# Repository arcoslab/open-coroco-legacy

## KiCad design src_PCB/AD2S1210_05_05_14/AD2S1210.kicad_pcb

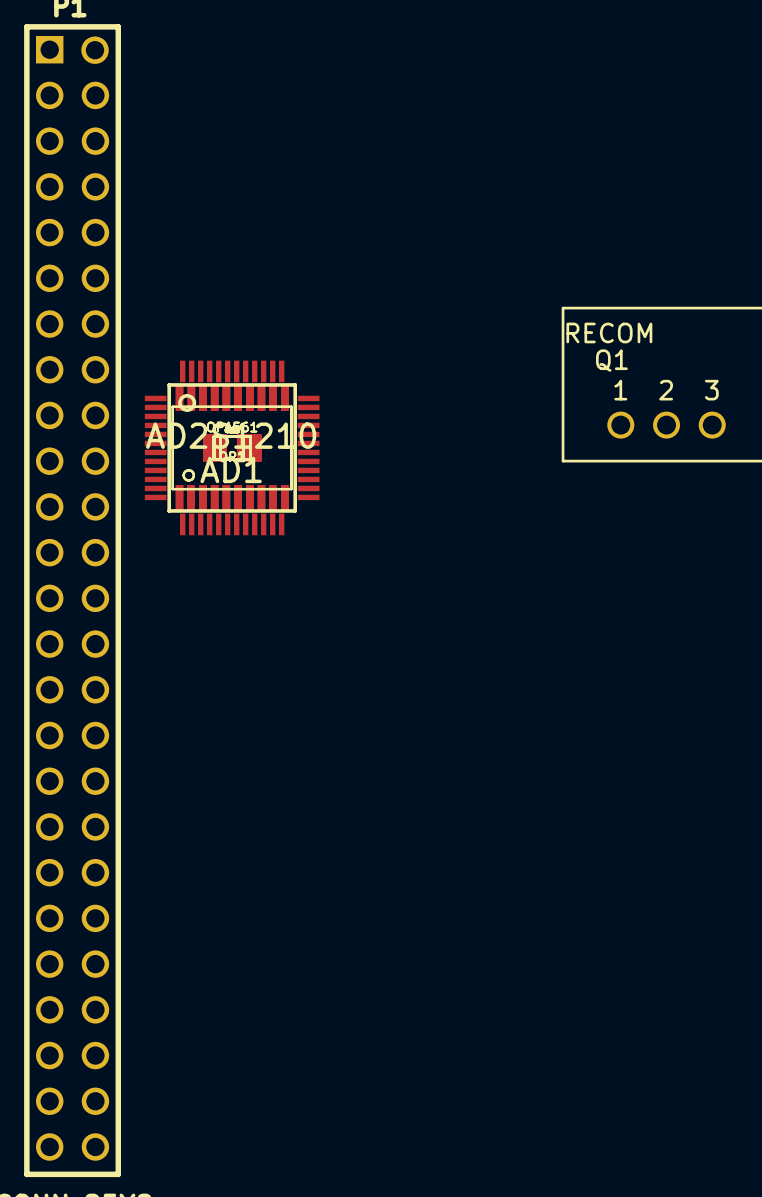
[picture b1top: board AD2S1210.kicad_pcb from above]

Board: 2 copper layers, 29 parts (0 on the bottom side), 40 nets, no tracks yet.

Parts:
AD1: AD2S1210; LQFP48
C2, C3, C5, C9, C18: 10n; c_0805
C4, C8: 20p; c_0805
C10: 4.7µ; c_0805
C11: 2.2µ; c_0805
C12, C13: 120p; c_0805
C16, C17: 100n; c_0805
OP1, OP2: OPA561; tssop-20
P1: CONN_25X2; PIN_ARRAY_STM32_25X2
Q1: RECOM; SIP-3
R1: 1k; c_0805
R2, R3: 15.4k; c_0805
R4, R5, R9, R11: 10k; c_0805
R6, R7: 390k; c_0805
R8, R10: 22k; c_0805

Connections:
/A0: AD1.36, AD1.37, P1.4, R1.1
/COS: AD1.45, P1.10
/COSLO: AD1.44, P1.12
/EXC: AD1.38, R5.1
/OUT_EXC: C13.1, OP2.7, P1.24, R3.1
/OUT_~EXC: C12.1, OP1.7, P1.22, R2.1
/SCLK: AD1.13, P1.38
/SDI: AD1.12, P1.40
/SDO: AD1.11, P1.37
/SIN: AD1.41, P1.18
/SINLO: AD1.42, P1.16
/V_DRIVE: AD1.3, P1.3
/~EXC: AD1.39, R4.1
/~SAMPLE: AD1.10, P1.9
/~WR: AD1.4, P1.13
GND: AD1.19, C16.2, C17.2, C18.2, OP1.5, OP2.5
unnamed: AD1.6, C3.2
unnamed: AD1.5, C3.1
unnamed: C9.2, C10.2
unnamed: AD1.18, C9.1, C10.1
unnamed: AD1.9, C4.2, C8.2
unnamed: C17.1, C18.1, Q1.2
unnamed: AD1.1, AD1.2, AD1.48, C2.2
unnamed: AD1.8, C8.1
unnamed: AD1.7, C4.1
unnamed: C16.1, Q1.1
unnamed: OP1.8, R6.2
unnamed: C12.2, OP1.3, R2.2, R4.2
unnamed: OP2.8, R7.2
unnamed: C13.2, OP2.3, R3.2, R5.2
unnamed: OP2.4, R11.2
unnamed: OP2.6, R7.1, R10.1
unnamed: AD1.33, C11.2, R1.2
unnamed: OP2.2, R10.2, R11.1
unnamed: AD1.43, C5.1
unnamed: AD1.40, C5.2
unnamed: AD1.46, C2.1
unnamed: OP1.2, R8.2, R9.1
unnamed: OP1.4, R9.2
unnamed: OP1.6, R6.1, R8.1

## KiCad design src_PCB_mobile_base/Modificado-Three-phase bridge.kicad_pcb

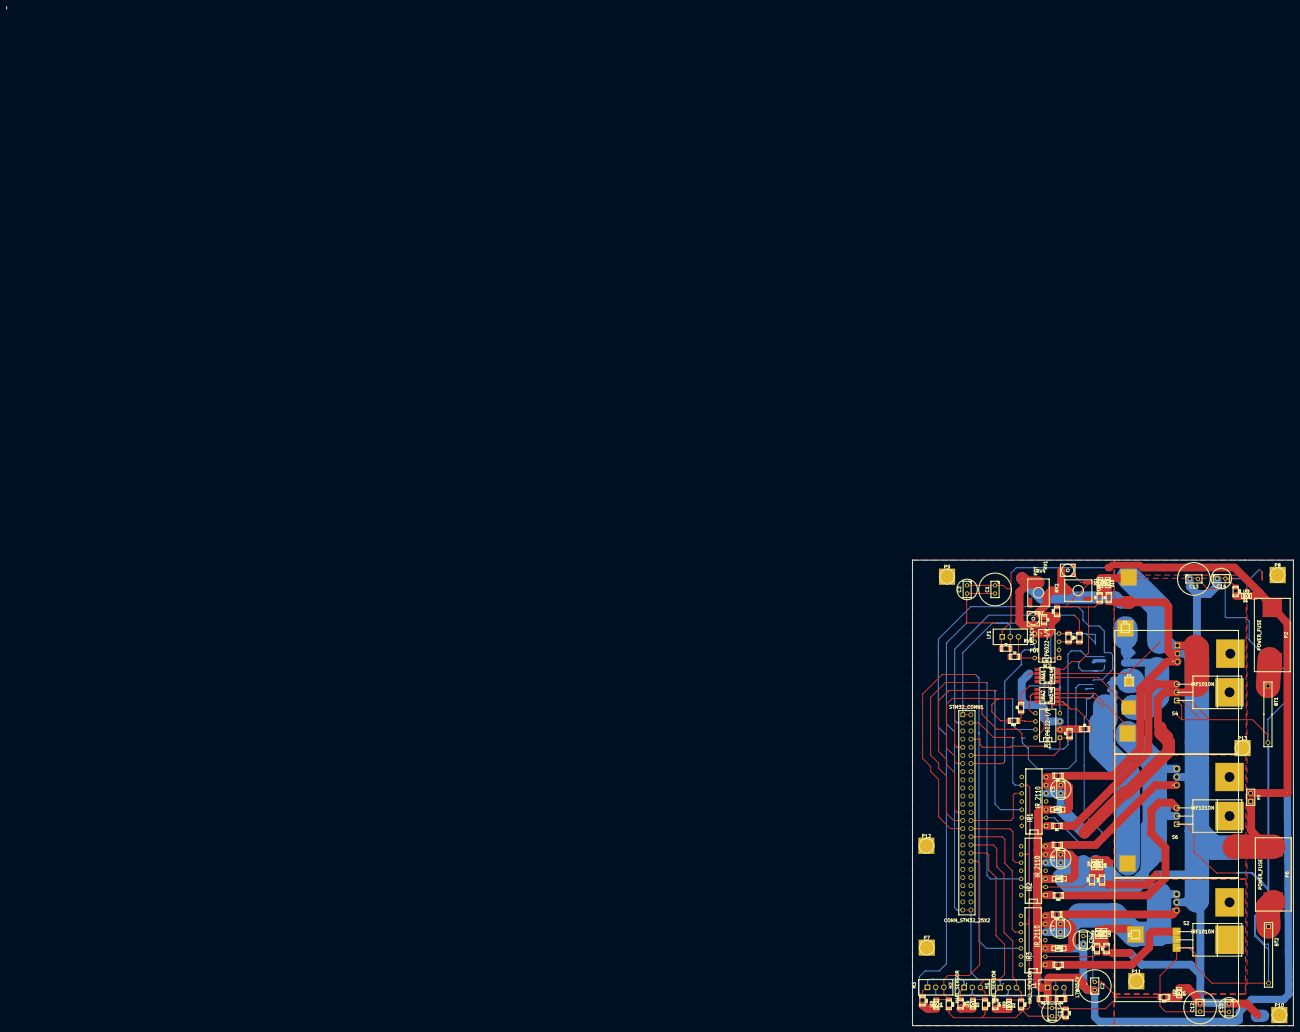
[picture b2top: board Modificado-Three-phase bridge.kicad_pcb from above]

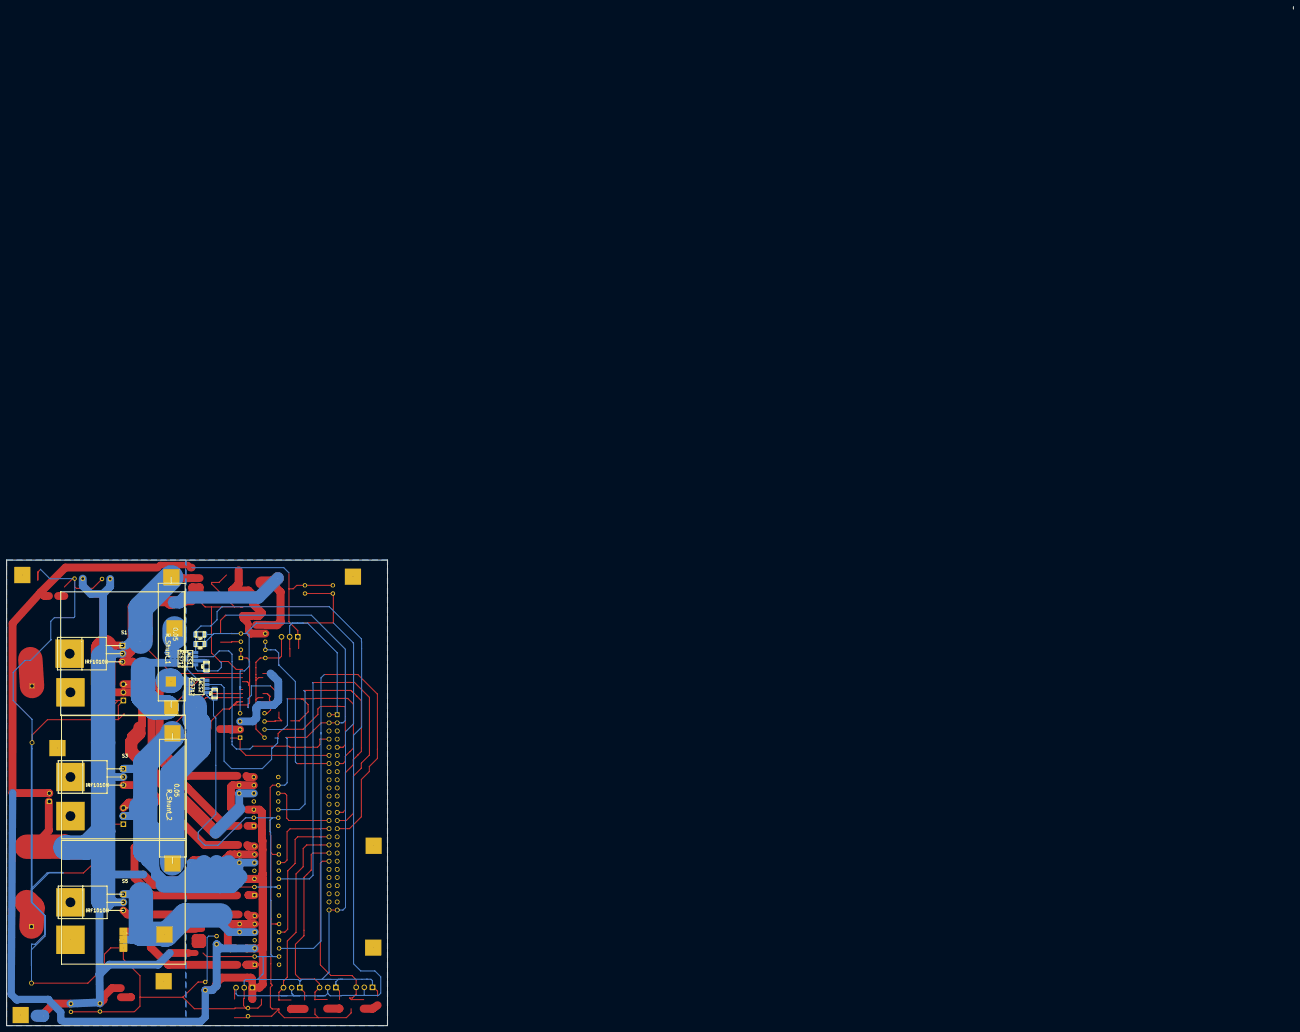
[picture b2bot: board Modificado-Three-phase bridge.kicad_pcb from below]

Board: 2 copper layers, 118.9 x 145.3 mm, 105 parts (11 on the bottom side), 61 nets.

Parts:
1N1, 1N2, 1N3: 1N4003; SOD-123
ACS1, ACS2: ACS712
BT1: BATTERY_12V; Battery_2x1
BT2: BATTERY_48; Battery_2x1
C1, C2, C12, C13: 1000uF; 10mm_C
C3, C4, C5, C6, C14, C15, C17: 100uF; 6mm_C
C7: 100u; 6mm_C
C8, C10, C18, C20: 0.1uF; c_1206
C9: 2.2uF; c_1206
C11: 0.33uF; c_1206
C16: 10uF; c_1206
C19, C21: 1nF; c_1206
D1, D2, D3, D4, D5, D6, D7, D8, D9, D10, D11: LED; LED-1206
H1, H2, H3: HALL_SENSOR; TO220_small_Heatsink_stand_reduced_area
INA1, INA2: INA148; INA_148
IR1, IR2, IR3: IR_2110; DIP-14__300
L1: L7805CV; TO220_small_Heatsink_stand_reduced_area
LF1: LF33CV; TO220_small_Heatsink_stand_reduced_area
M1, M2: MCP6022-I/P; DIP-8__300
P1, P4, P5: CONN_1; PIN_ARRAY_1
P2, P6: POWER_FUSE; fuse_holder_SMD
P3: CONN_2; pin_2
P7, P8, P9, P10, P11, P12, P13: CONN_1; 1pin
R1, R3, R5, R7, R8, R9, R10, R11, R12, R13, R15, R17, R18, R21, R22, R23, R24, R25, R26: 1k; R_1206
R2, R4, R14, R16, R19, R20: 36; R_1206
R6: 3.9k; R_1206
R27, R28: R; R_1206
RV1, RV3: POT; Trimmer_20K_1.5mmW_4.5mmL_3.8mmH
RV2, RV4: POT; Trimmer_100K_5.21mmW_6.71mmL
R_Shunt_1, R_Shunt_2: 0.05; R_Shunt
S1, S2, S3, S4, S5, S6: IRF1010N; TO220_Big_Heat_Sink_Drain_Sink
STM32_CONN1: CONN_STM32_25X2; PIN_ARRAY_STM32_25X2

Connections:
+3.3V: C9.1, INA1.7, INA2.7, LF1.2, M1.8, M2.8
+5V: ACS1.8, ACS2.8, C10.2, C18.1, C20.1, H1.3, H2.3, H3.3, L1.2
+48V: C12.1, C13.1, C14.1, C15.1, D5.1, P3.1, P6.1, R1.2, R6.1, R13.2, R17.2, RV3.1, RV4.1, S1.3, S3.3, S5.3
GND: ACS1.5, ACS2.5, BT1.2, BT2.2, C1.2, C2.2, C3.2, C4.2, C8.1, C9.2, C10.1, C11.1, C12.2, C13.2, C14.2, C15.2, C16.2, C17.2, C18.2, C19.2, C20.2, C21.2, H1.1, H2.1, H3.1, INA1.4, INA2.4, IR1.2, IR1.13, IR2.2, IR2.13, IR3.2, IR3.13, L1.3, LF1.3, M1.4, M2.4, R3.2, R10.1, R12.2, R15.2, R18.2, R24.2, R25.2, R26.2, R27.1, R28.2, RV1.2, RV2.2, S2.1, S4.1, S6.1, STM32_CONN1.1, STM32_CONN1.2, STM32_CONN1.49, STM32_CONN1.50
unnamed: IR3.12, STM32_CONN1.29
unnamed: D2.1, H1.2, R21.2, STM32_CONN1.34
unnamed: D3.1, H2.2, R22.2, STM32_CONN1.36
unnamed: IR1.10, STM32_CONN1.28
unnamed: IR1.1, R4.1
unnamed: IR1.7, R2.1
unnamed: 1N1.2, C5.1, IR1.6
unnamed: M2.6, M2.7, STM32_CONN1.14
unnamed: IR2.10, STM32_CONN1.30
unnamed: IR3.10, STM32_CONN1.32
unnamed: IR1.12, STM32_CONN1.25
unnamed: IR2.12, STM32_CONN1.27
unnamed: BT2.1, P6.2
unnamed: BT1.1, P2.2
unnamed: ACS1.6, C19.1
unnamed: M1.1, R9.2, STM32_CONN1.12
unnamed: D6.2, D7.1, R17.1, R18.1
unnamed: D8.2, D9.1, R13.1, R15.1
unnamed: INA2.6, M1.5
unnamed: D10.2, D11.1, R1.1, R3.1
unnamed: M1.7, R11.1, STM32_CONN1.13
unnamed: M2.5, R6.2, R10.2, RV1.1, RV2.1, RV3.2, RV4.2
unnamed: M2.3, R7.2, R12.1
unnamed: IR2.1, R16.1
unnamed: IR2.7, R14.1
unnamed: 1N2.2, C6.1, IR2.6
unnamed: ACS1.3, ACS1.4, INA1.2, R_Shunt_1.2
unnamed: IR3.1, R20.1
unnamed: IR3.7, R19.1
unnamed: 1N3.2, C7.1, IR3.6
unnamed: M1.6, R8.2, R11.2
unnamed: INA1.6, M1.3
unnamed: M1.2, R5.2, R9.1
unnamed: D4.1, H3.2, R23.2, STM32_CONN1.38
unnamed: ACS1.7, STM32_CONN1.8
unnamed: C6.2, D8.1, D9.2, INA2.3, IR2.5, R_Shunt_2.1, S3.1, S6.3
unnamed: C5.2, D10.1, D11.2, INA1.3, IR1.5, R_Shunt_1.1, S1.1, S4.3
unnamed: C7.2, D6.1, D7.2, IR3.5, P5.1, S2.3, S5.1
unnamed: ACS1.1, ACS1.2, P1.1
unnamed: ACS2.1, ACS2.2, P4.1
unnamed: ACS2.3, ACS2.4, INA2.2, R_Shunt_2.2
unnamed: ACS2.6, C21.1
unnamed: D5.2, R27.2
unnamed: D1.2, R28.1
unnamed: ACS2.7, STM32_CONN1.9
unnamed: R14.2, S3.2
unnamed: INA1.1, INA2.1, M2.1, M2.2, R5.1, R8.1
unnamed: R16.2, S6.2
unnamed: R2.2, S1.2
unnamed: R4.2, S4.2
unnamed: R20.2, S2.2
unnamed: R19.2, S5.2
unnamed: D3.2, R25.1
unnamed: D4.2, R26.1
unnamed: D2.2, R24.1
VCC: 1N1.1, 1N2.1, 1N3.1, C1.1, C2.1, C3.1, C4.1, C8.2, C11.2, D1.1, IR1.3, IR2.3, IR3.3, L1.1, LF1.1, P2.1, P3.2
VDD: C16.1, C17.1, IR1.9, IR2.9, IR3.9, R7.1, R21.1, R22.1, R23.1, STM32_CONN1.3, STM32_CONN1.4

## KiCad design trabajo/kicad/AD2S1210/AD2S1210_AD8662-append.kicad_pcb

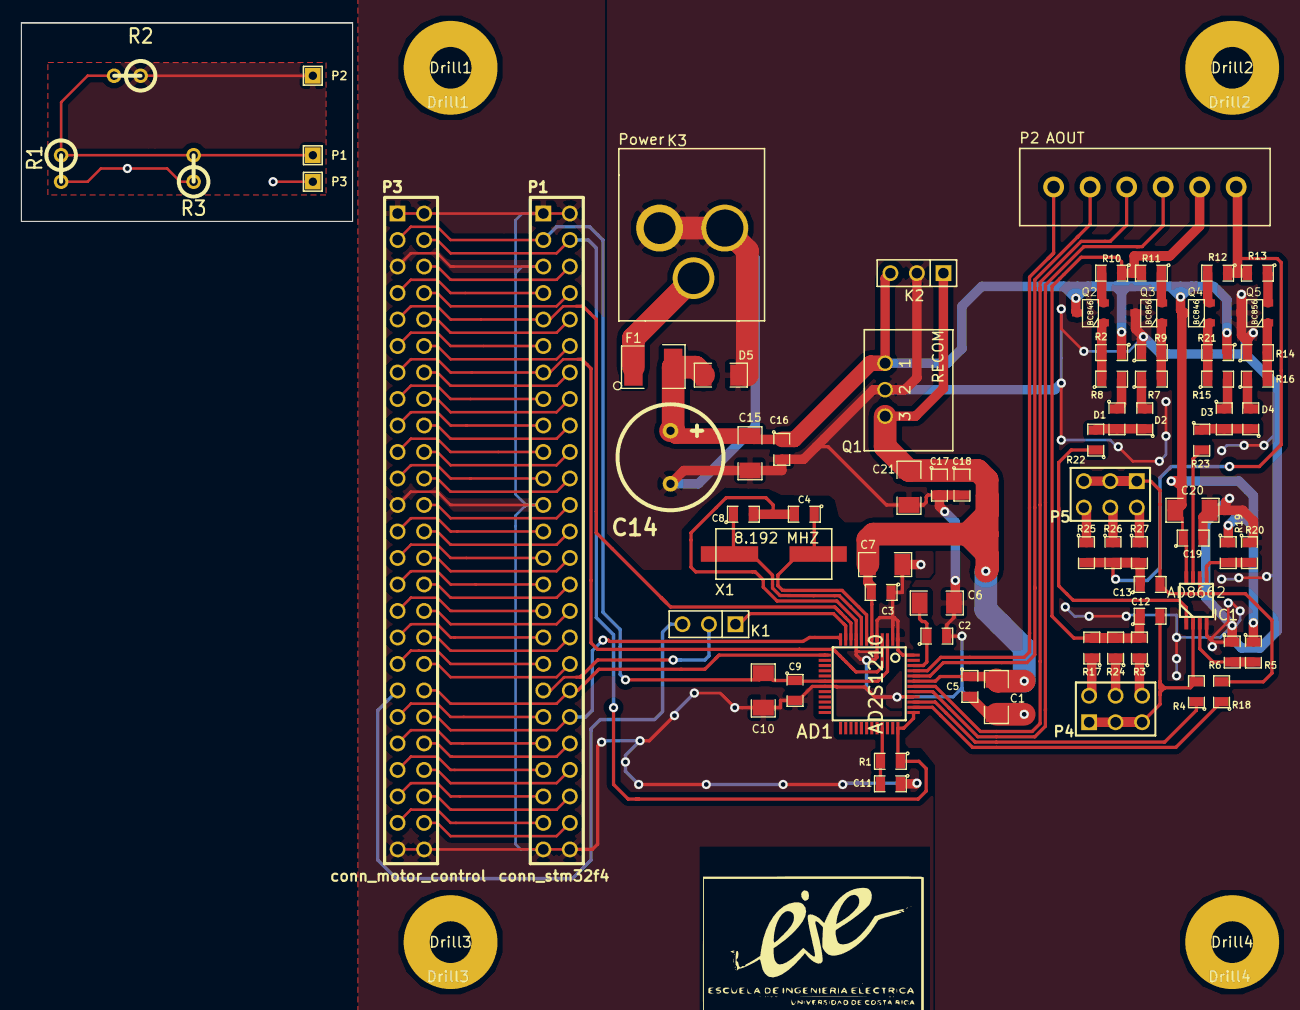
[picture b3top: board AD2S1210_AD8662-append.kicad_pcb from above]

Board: 2 copper layers, 31.8 x 19.1 mm, 80 parts (0 on the bottom side), 90 nets.

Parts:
AD1: AD2S1210; LQFP48
C1, C7, C10: 4.7µ; SM1206
C2, C3, C5, C9, C18: 10n; SM0805
C4, C8: 20p; SM0805
C6, C15, C20, C21: 10µ; SM1206
C11: 2.2µ; SM0805
C12, C13: 120p; SM0805
C14: 220µ; Elko_vert_DM10_RM5_CopperClear
C16, C17, C19: 100n; SM0805
D1, D2, D3, D4: DIODE; SM0805
D5: DIODE; SM1206
Drill1: Drill1; drill_4mm
Drill2: Drill2; drill_4mm
Drill3: Drill3; drill_4mm
Drill4: Drill4; drill_4mm
F1: FUSE; SM1812E
IC1: AD8662; MSOP_8
K1: JP_1; PIN_ARRAY_3X1
K2: V_control; PIN_ARRAY_3X1
K3: Power; power_jack
P1, P2, P3: CONN_1; SIL-1
P1#2: conn_stm32f4; PIN_ARRAY_STM32_25X2
P2#2: AOUT; pin_array_6_3.5mm
P3#2: conn_motor_control; PIN_ARRAY_STM32_25X2
P4: JP_2; pin_array_3x2
P5: JP_3; pin_array_3x2
Q1: RECOM; SIP-3
Q2, Q4: BC846; SOT23
Q3, Q5: BC856; SOT23
R1: 10K; R1
R1#2: 1k; SM0805
R2: 1K; R1
R2#2, R9, R14, R21: 2.2k; SM0805
R3: 3,3K; R1
R3#2, R25: 8.66k; SM0805
R4, R6, R18, R20: 10k; SM0805
R5, R19: 22k; SM0805
R7, R8, R15, R16: 3.3k; SM0805
R10, R11, R12, R13: 4.7k; SM0805
R17, R27: 13.6k; SM0805
R22, R23: 0k; SM0805
R24, R26: 15.4k; SM0805
X1: 8.192 MHZ; crystal_ATS

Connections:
+1.8V: P2.1, R2.1
+5V: AD1.6, AD1.43, C1.1, C3.2, C5.1, C7.2, C17.1, C18.1, C21.1, K2.1, Q1.3
/12V_a: F1.1, K3.3
/A0: AD1.36, AD1.37, P1#2.4, P3#2.4, R1#2.1
/COS: AD1.45, P2#2.6
/COSLO: AD1.44, P2#2.5
/EXC: AD1.38, R18.1
/Hall3: K1.3, P3#2.37
/NC: P1#2.48, P3#2.48
/NRST: P1#2.6, P3#2.6
/OUT_EXC: C13.1, P2#2.1, R12.1, R13.2, R25.2, R26.2, R27.2
/OUT_~EXC: C12.1, P2#2.2, R3#2.2, R10.1, R11.2, R17.2, R24.2
/PA0: P1#2.12, P3#2.12
/PA1: P1#2.11, P3#2.11
/PA2: P1#2.14, P3#2.14
/PA4: P1#2.16, P3#2.16
/PA5: P1#2.15, P3#2.15
/PA6: P1#2.18, P3#2.18
/PA7: P1#2.17, P3#2.17
/PB0: P1#2.22, P3#2.22
/PB1: P1#2.21, P3#2.21
/PB2: P1#2.24, P3#2.24
/PB10: P1#2.34, P3#2.34
/PB11: P1#2.35, P3#2.35
/PB12: P1#2.36, P3#2.36
/PB15: P1#2.39, P3#2.39
/PC0: P1#2.8, P3#2.8
/PC1: P1#2.7, P3#2.7
/PC2: P1#2.10, P3#2.10
/PC4: P1#2.20, P3#2.20
/PC5: P1#2.19, P3#2.19
/PD9: P1#2.41, P3#2.41
/PD10: P1#2.42, P3#2.42
/PD11: P1#2.43, P3#2.43
/PD12: P1#2.44, P3#2.44
/PD13: P1#2.45, P3#2.45
/PD14: P1#2.46, P3#2.46
/PD15: P1#2.47, P3#2.47
/PE7: P1#2.25, P3#2.25
/PE8: P1#2.26, P3#2.26
/PE9: P1#2.27, P3#2.27
/PE10: P1#2.28, P3#2.28
/PE11: P1#2.29, P3#2.29
/PE12: P1#2.30, P3#2.30
/PE13: P1#2.31, P3#2.31
/PE14: P1#2.32, P3#2.32
/PE15: P1#2.33, P3#2.33
/SCLK: AD1.13, P1#2.38, P3#2.38
/SDI: AD1.12, P1#2.40, P3#2.40
/SDO: AD1.11, K1.1
/SDO_HALL3: K1.2, P1#2.37
/SIN: AD1.41, P2#2.3
/SINLO: AD1.42, P2#2.4
/V_DRIVE: AD1.3, AD1.18, C9.1, C10.1, P1#2.3, P3#2.3
/pin1: P1.1, R1.1, R2.2, R3.2
/~EXC: AD1.39, R4.1
/~SAMPLE: AD1.10, P1#2.9, P3#2.9
/~WR: AD1.4, P1#2.13, P3#2.13
GND: AD1.1, AD1.2, AD1.5, AD1.9, AD1.19, AD1.40, AD1.48, C1.2, C2.2, C3.1, C4.2, C5.2, C6.2, C7.1, C8.2, C9.2, C10.2, C11.1, C14.2, C15.2, C16.2, C17.2, C18.2, C19.2, C20.2, C21.2, D5.1, IC1.4, K2.2, K3.1, K3.2, P1#2.1, P1#2.2, P1#2.5, P1#2.23, P1#2.49, P1#2.50, P3#2.1, P3#2.2, P3#2.5, P3#2.23, P3#2.49, P3#2.50, Q1.2, Q3.3, Q5.3, R6.1, R9.1, R14.1, R20.1
unnamed: AD1.33, C11.2, R1#2.2
unnamed: D4.2, R16.1
unnamed: D3.1, R15.2
unnamed: P3.1, Q4.1, R1.2, R3.1, R15.1, R21.2
unnamed: D3.2, D4.1, R23.1
unnamed: Q5.2, R13.1
unnamed: Q4.2, R12.2
unnamed: Q5.1, R14.2, R16.2
unnamed: IC1.5, R19.2, R20.2
unnamed: P5.2, R27.1
unnamed: C13.2, IC1.6, P5.1, P5.3, P5.5, R18.2
unnamed: P5.4, R26.1
unnamed: P5.6, R25.1
unnamed: IC1.3, R5.2, R6.2
unnamed: IC1.7, R23.2
unnamed: P4.2, R17.1
unnamed: P4.4, R24.1
unnamed: P4.6, R3#2.1
unnamed: AD1.46, C2.1, C6.1
unnamed: Q3.2, R11.1
unnamed: IC1.1, R22.1
unnamed: C12.2, IC1.2, P4.1, P4.3, P4.5, R4.2
unnamed: D1.1, R8.2
unnamed: Q2.2, R10.2
unnamed: Q3.1, R7.2, R9.2
unnamed: Q2.1, R2#2.2, R8.1
unnamed: D2.2, R7.1
unnamed: D1.2, D2.1, R22.2
unnamed: AD1.7, C4.1, X1.1
unnamed: AD1.8, C8.1, X1.2
VCC: C14.1, C15.1, C16.1, C19.1, C20.1, D5.2, F1.2, IC1.8, K2.3, Q1.1, Q2.3, Q4.3, R2#2.1, R5.1, R19.1, R21.1
